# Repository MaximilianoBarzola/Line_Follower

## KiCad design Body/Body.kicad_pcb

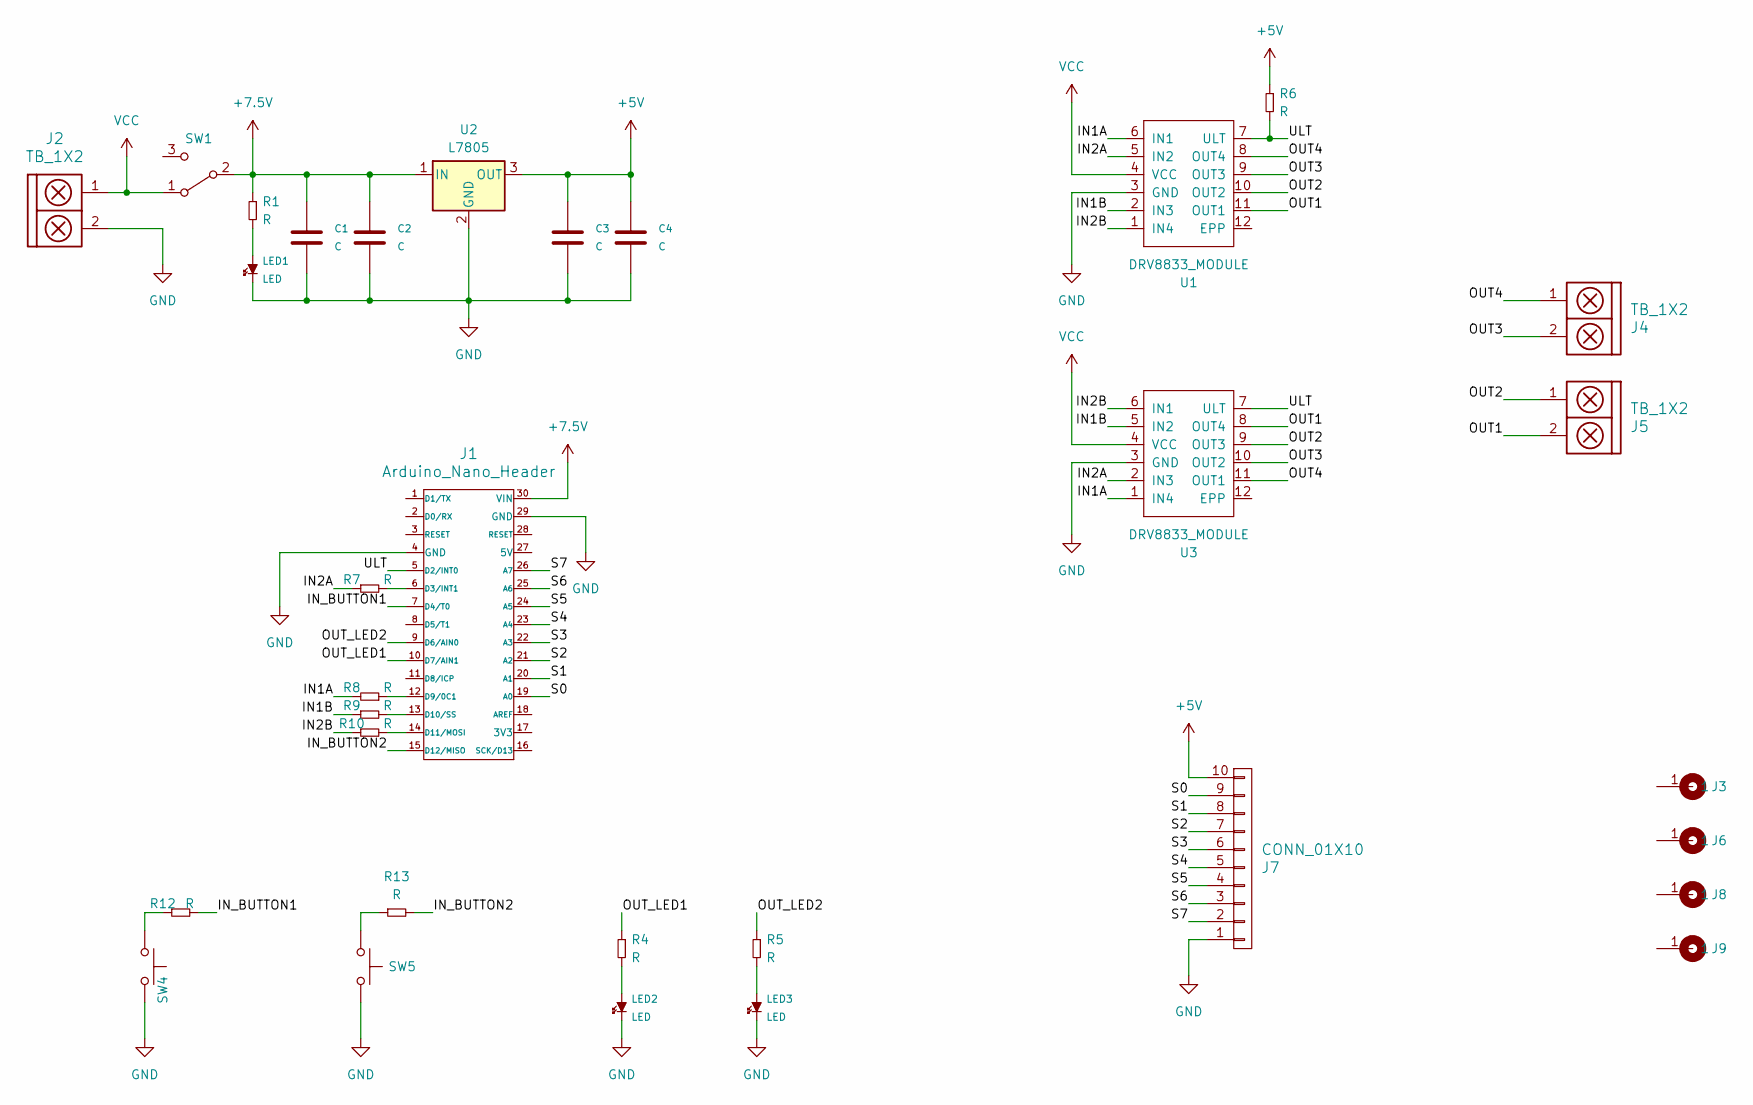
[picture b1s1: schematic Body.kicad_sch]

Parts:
C1, C4: C; CAP_ELEC_5x11mm
C2, C3: C; CAP_0.2
J1: Arduino_Nano_Header; arduino_nano_header
J2: TB_1X2; XT30AWM
J3, J6: Cable_PAD; Pololu_Micro_Bracket_Wheel_42mm
J4, J5: TB_1X2; BORNERA2_AZUL
J7: CONN_01X10; Pin_Header_Wire_10
J8, J9: Cable_PAD; Tornillo_M3_8mm
LED1: LED; led_5mm_red
LED2, LED3: LED; led_5mm_green
R1, R4, R5, R6, R7, R8, R9, R10, R12, R13: R; RES0.3
SW1: SW_SPDT; SW_SPDT_TH_Vertical
SW4, SW5: SW_Push; Button
U1, U3: DRV8833_MODULE
U2: L7805; TO-220-3_Vertical

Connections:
+5V: C3.1, C4.1, J7.10, R6.1, U2.3 (OUT)
+7.5V: C1.1, C2.1, J1.30 (VIN), R1.1, SW1.2 (B), U2.1 (IN)
/IN1A: R8.2, U1.6 (IN1), U3.1 (IN4)
/IN1B: R9.1, U1.2 (IN3), U3.5 (IN2)
/IN2A: R7.1, U1.5 (IN2), U3.2 (IN3)
/IN2B: R10.1, U1.1 (IN4), U3.6 (IN1)
/IN_BUTTON1: J1.7 (D4/T0), R12.2
/IN_BUTTON2: J1.15 (D12/MISO), R13.2
/OUT1: J5.2, U1.11 (OUT1), U3.8 (OUT4)
/OUT2: J5.1, U1.10 (OUT2), U3.9 (OUT3)
/OUT3: J4.2, U1.9 (OUT3), U3.10 (OUT2)
/OUT4: J4.1, U1.8 (OUT4), U3.11 (OUT1)
/OUT_LED1: J1.10 (D7/AIN1), R4.1
/OUT_LED2: J1.9 (D6/AIN0), R5.1
/S0: J1.19 (A0), J7.9
/S1: J1.20 (A1), J7.8
/S2: J1.21 (A2), J7.7
/S3: J1.22 (A3), J7.6
/S4: J1.23 (A4), J7.5
/S5: J1.24 (A5), J7.4
/S6: J1.25 (A6), J7.3
/S7: J1.26 (A7), J7.2
/ULT: J1.5 (D2/INT0), R6.2, U1.7 (ULT), U3.7 (ULT)
GND: C1.2, C2.2, C3.2, C4.2, J1.4 (GND), J1.29 (GND), J2.2, J7.1, LED1.2 (K), LED2.2 (K), LED3.2 (K), SW4.2, SW5.2, U1.3 (GND), U2.2 (GND), U3.3 (GND)
unnamed: J1.6 (D3/INT1), R7.2
unnamed: J1.12 (D9/0C1), R8.1
unnamed: J1.13 (D10/SS), R9.2
unnamed: J1.14 (D11/MOSI), R10.2
unnamed: LED1.1 (A), R1.2
unnamed: LED2.1 (A), R4.2
unnamed: LED3.1 (A), R5.2
unnamed: R12.1, SW4.1
unnamed: R13.1, SW5.1
VCC: J2.1, SW1.1 (A), U1.4 (VCC), U3.4 (VCC)

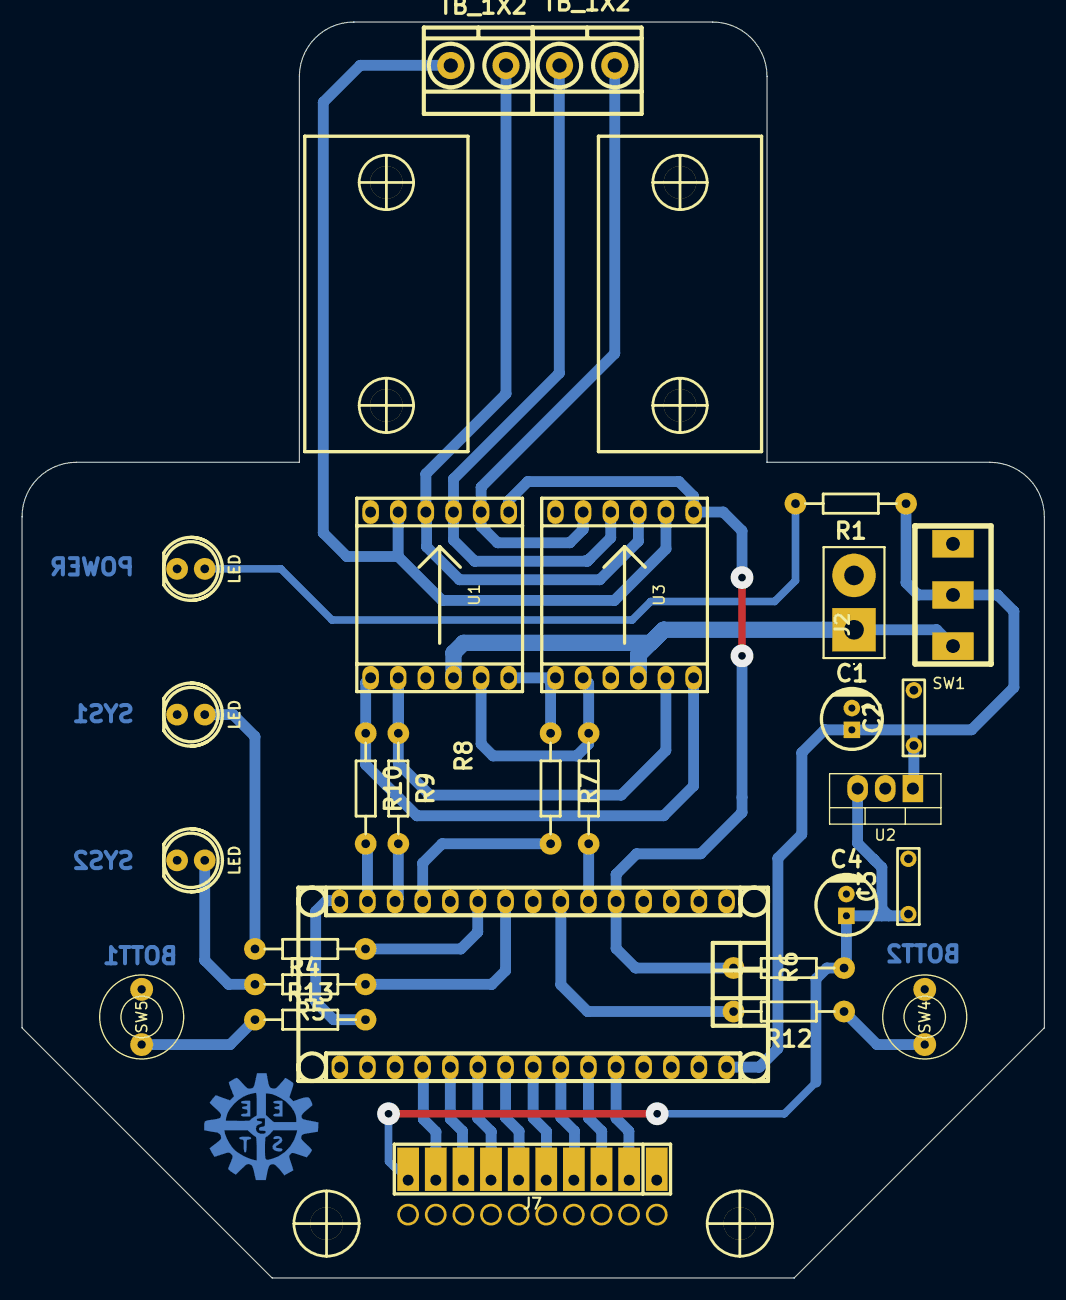
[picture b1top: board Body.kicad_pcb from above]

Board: 2 copper layers, 94.0 x 115.5 mm, 32 parts (0 on the bottom side), 34 nets.

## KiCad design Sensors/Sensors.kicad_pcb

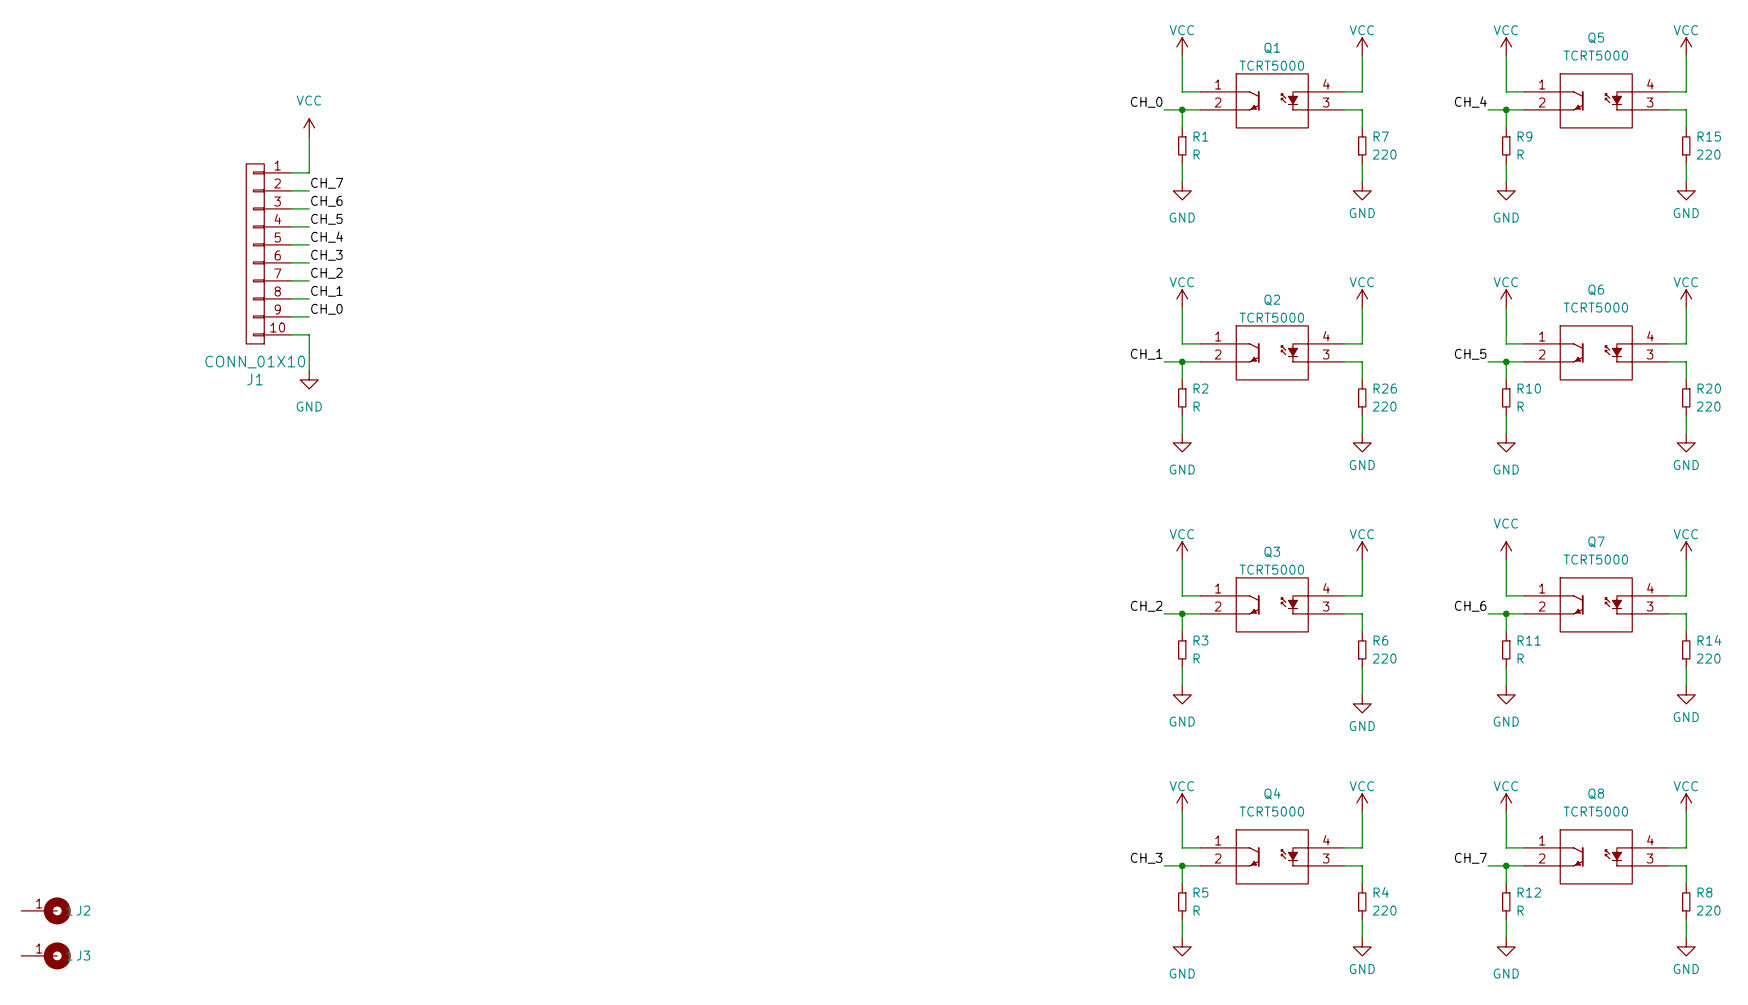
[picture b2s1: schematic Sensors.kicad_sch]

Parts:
J1: CONN_01X10; Pin_Header_Wire_10
J2, J3: Cable_PAD; Tornillo_M3_8mm
Q1, Q2, Q3, Q4, Q5, Q6, Q7, Q8: TCRT5000; TCRT5000L; Manufacturer_Part_Number TCRT5000; Mouser Part Number 782-TCRT5000
R1, R2, R3, R5, R9, R10, R11, R12: R; RES0.3
R4, R6, R7, R8, R14, R15, R20, R26: 220; RES0.3

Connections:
/CH_0: J1.9, Q1.2 (E), R1.1
/CH_1: J1.8, Q2.2 (E), R2.1
/CH_2: J1.7, Q3.2 (E), R3.1
/CH_3: J1.6, Q4.2 (E), R5.1
/CH_4: J1.5, Q5.2 (E), R9.1
/CH_5: J1.4, Q6.2 (E), R10.1
/CH_6: J1.3, Q7.2 (E), R11.1
/CH_7: J1.2, Q8.2 (E), R12.1
GND: J1.10, R1.2, R2.2, R3.2, R4.1, R5.2, R6.1, R7.1, R8.1, R9.2, R10.2, R11.2, R12.2, R14.1, R15.1, R20.2, R26.1
unnamed: Q1.3 (K), R7.2
unnamed: Q2.3 (K), R26.2
unnamed: Q3.3 (K), R6.2
unnamed: Q4.3 (K), R4.2
unnamed: Q5.3 (K), R15.2
unnamed: Q6.3 (K), R20.1
unnamed: Q7.3 (K), R14.2
unnamed: Q8.3 (K), R8.2
VCC: J1.1, Q1.1 (C), Q1.4 (A), Q2.1 (C), Q2.4 (A), Q3.1 (C), Q3.4 (A), Q4.1 (C), Q4.4 (A), Q5.1 (C), Q5.4 (A), Q6.1 (C), Q6.4 (A), Q7.1 (C), Q7.4 (A), Q8.1 (C), Q8.4 (A)

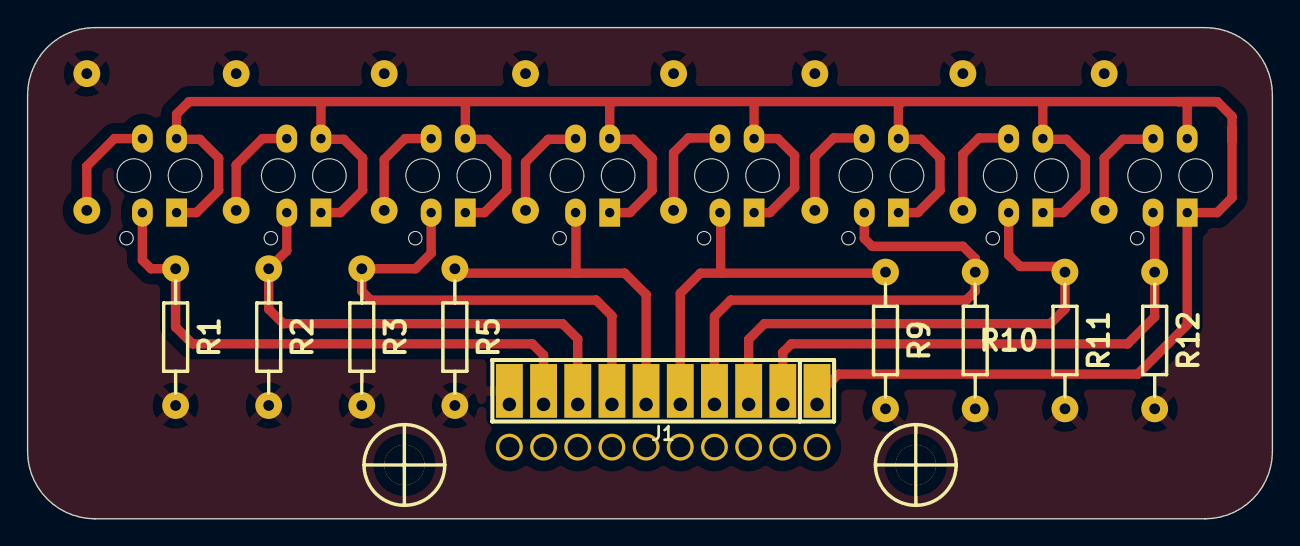
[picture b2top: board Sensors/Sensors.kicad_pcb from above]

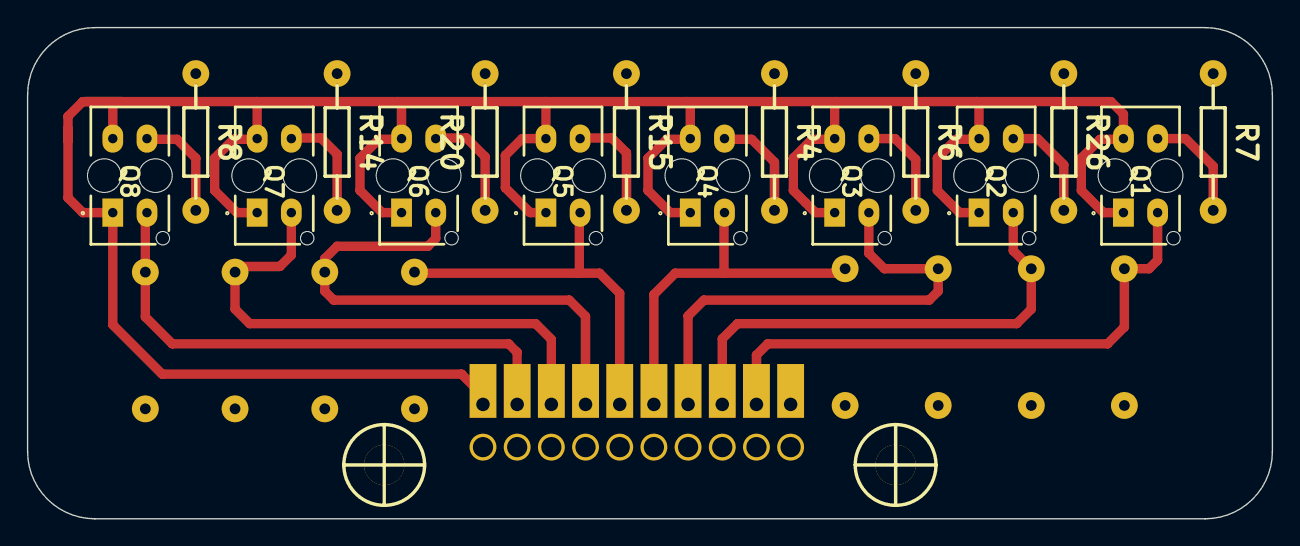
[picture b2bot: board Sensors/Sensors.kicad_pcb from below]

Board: 2 copper layers, 92.5 x 36.5 mm, 27 parts (16 on the bottom side), 18 nets.

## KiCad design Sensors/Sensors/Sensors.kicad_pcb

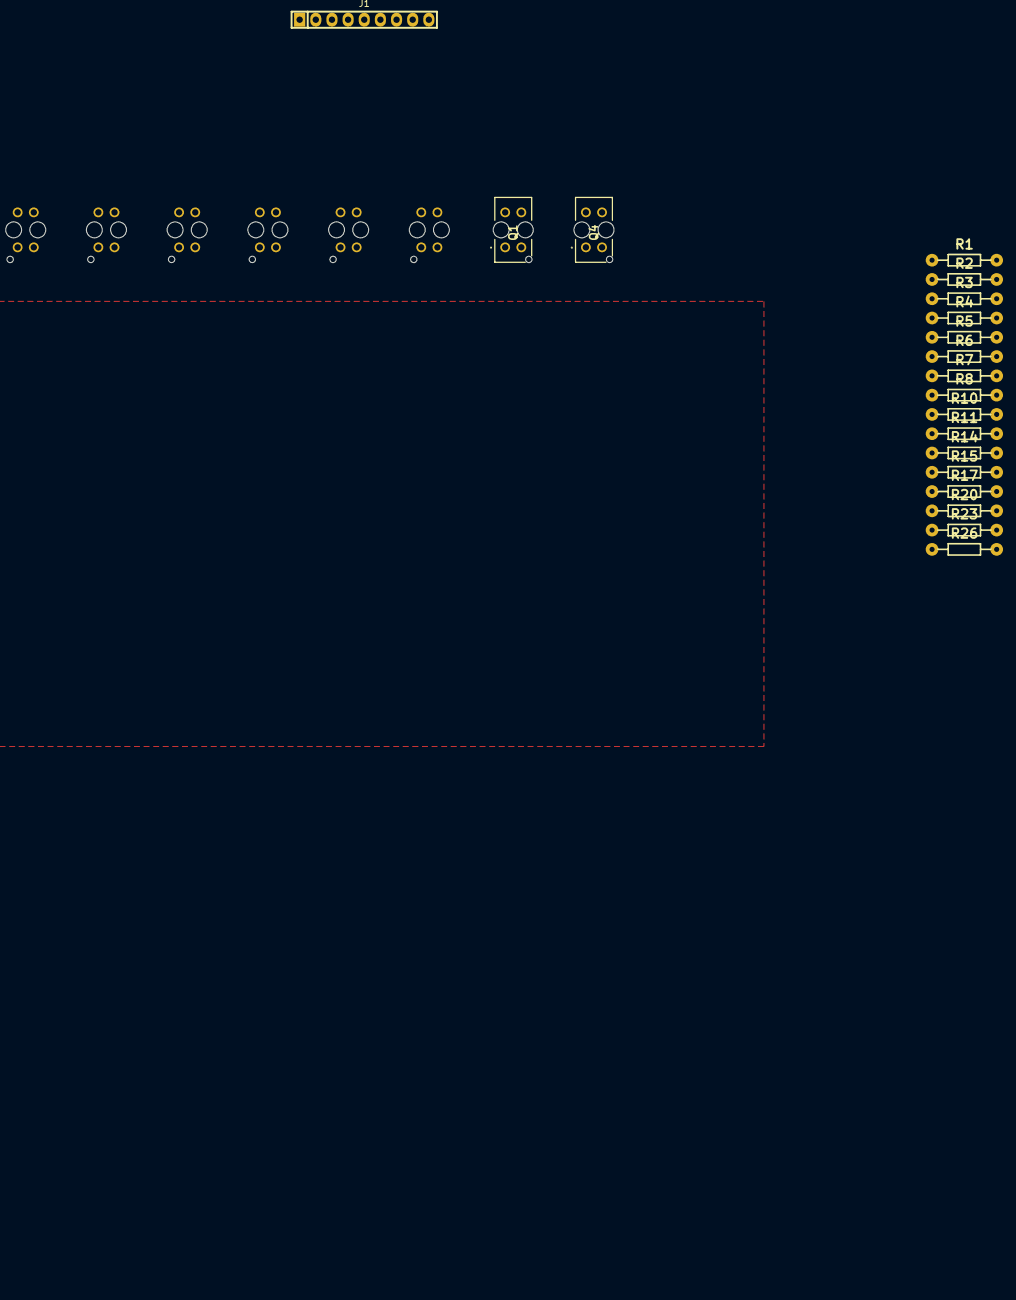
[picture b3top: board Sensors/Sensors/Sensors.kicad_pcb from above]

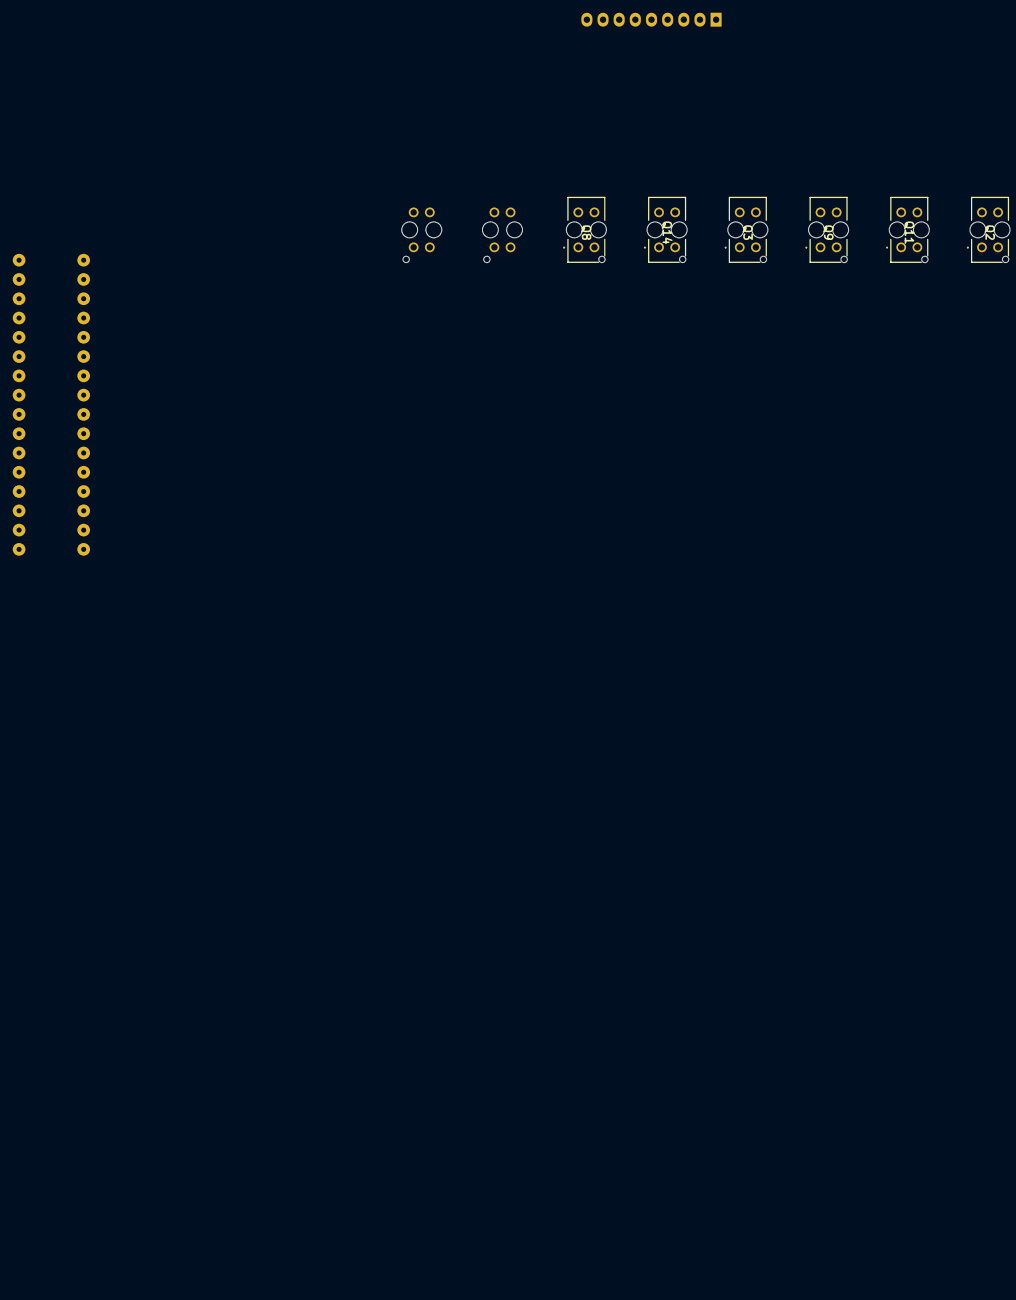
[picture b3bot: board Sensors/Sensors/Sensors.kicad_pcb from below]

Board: 2 copper layers, 25 parts (6 on the bottom side), 18 nets, no tracks yet.

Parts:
J1: CONN_01X09; PIN_STRIP_9
Q1, Q2, Q3, Q4, Q8, Q9, Q11, Q14: TCRT5000; TCRT5000L
R1, R2, R3, R5, R10, R11, R17, R23: 10k; RES0.3
R4, R6, R7, R8, R14, R15, R20, R26: 220; RES0.3

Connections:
/Y0: Q2.2 (E), R1.1
/Y1: Q8.2 (E), R10.1
/Y2: Q14.2 (E), R23.1
/Y3: Q11.2 (E), R17.1
/Y4: Q3.2 (E), R2.1
/Y5: Q9.2 (E), R11.1
/Y6: Q1.2 (E), R3.1
/Y7: Q4.2 (E), R5.1
GND: J1.9, R1.2, R2.2, R3.2, R4.1, R5.2, R6.1, R7.1, R8.1, R10.2, R11.2, R14.1, R15.1, R17.2, R20.2, R23.2, R26.1
unnamed: Q1.3 (K), R4.2
unnamed: Q2.3 (K), R6.2
unnamed: Q3.3 (K), R7.2
unnamed: Q4.3 (K), R8.2
unnamed: Q8.3 (K), R14.2
unnamed: Q9.3 (K), R15.2
unnamed: Q11.3 (K), R20.1
unnamed: Q14.3 (K), R26.2
VCC: J1.1, Q1.1 (C), Q1.4 (A), Q2.1 (C), Q2.4 (A), Q3.1 (C), Q3.4 (A), Q4.1 (C), Q4.4 (A), Q8.1 (C), Q8.4 (A), Q9.1 (C), Q9.4 (A), Q11.1 (C), Q11.4 (A), Q14.1 (C), Q14.4 (A)

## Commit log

2024-10-19 code
2025-01-22 pendrive files
2025-01-29 rev_0.0.1
2025-02-14 Rev. 1.0.0
2025-07-30 V1.0.0
2025-08-07 Code_rev1.1
2025-08-08 new code
2025-08-09 nFault Code
2025-09-04 Rev 1.0.1
2025-09-17 new_code
2025-10-07 code_optimization
2025-10-20 new_velocista
